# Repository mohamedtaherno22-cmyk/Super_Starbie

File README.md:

## Super Starbie ##
Super Starbie combines a Tamagotchi and an AI desktop pet into one project. Super Starbie displays monitored temperature and humidity (DHT-11), responds to button presses, and reacts to movement (MPU6050). It also features a built-in microphone (INMP411 MEMS) and a speaker, enabling TTS & STT for the AI version.

**Working Features & Features for the build week:** Theoretically, all the code is supposed to work. However, I couldn't test the firmware, especially for the AI voice chat, because I was not able to find a good emulator. I will edit the firmware and ensure that every last feature of the project works once the parts are here.

## Hardware

- **ESP32-C3 SuperMini:** MCU that processes sensor data, handles user inputs, controls the display, and provides wireless connectivity for AI features.

- **0.96" OLED Display:** A 4-pin I2C display for starbie.

- **2 Mechanical Switches:** Open the menu for the Tamagotchi, choosing options in the menu, etc.

- **MPU-6050 Motion Sensor:** A 6-axis gyroscope and accelerometer for motion detection.

- **DHT11 Temperature & Humidity Sensor:** Measures the surrounding temperature and humidity.

- **INMP441 MEMS Microphone:** An I2S digital microphone that captures audio input, enabling Speech-to-Text (STT) and voice interaction in AI mode.

- **LM386 Audio Amplifier:** Amplifies the audio signal to drive the speaker and provide audible responses.

- **Speaker:** Provides audio output for Text-to-Speech (TTS).

- **10KΩ Pull-up Resistor:**.

## BOM TABLE

| Item | Qty | Supplier | Cost/Item | Total Cost |
|---|:---:|---|---:|---:|
| MPU-6050 Gyroscope + Accelerometer | 1 | [Ram Electronics](https://www.ram-e-shop.com/shop/kit-imu-mpu6050-gy521-imu-6-dof-mpu-6050-gyroscope-accelerometer-sensor-module-7076) | $3.34 | $3.34 |
| DHT-11 Temperature & Humidity Sensor | 1 | [Ram Electronics](https://www.ram-e-shop.com/shop/sen-dht11-dht-11-temperature-humidity-sensor-asair-original-brand-7093) | $1.16 | $1.16 |
| 0.96" OLED 4-pin I2C Display | 1 | [Future Electronics](https://store.fut-electronics.com/products/1-3-128x64-oled-display-module-i-c-iic-sh1106) | $4.83 | $4.83 |
| Custom PCB | 1 | [Metanoia](https://metanoia-eg.com/pcbaf/) | $8.36 | $8.36 |
| Mechanical Keyboard Switches | 2 | [Amazon](https://www.amazon.eg/) | $1.16 | $2.32 |
| 10KΩ Resistors (2 pcs) | 1 | [Amazon](https://www.amazon.eg/) | $0.10 | $0.10 |
| ESP32-C3 SuperMini | 1 | [Amazon](https://www.amazon.eg/) | $5.95 | $5.95 |
| LM386 Audio Amplifier Module | 1 | [Ram Electronics](https://www.ram-e-shop.com/shop/kit-amp-lm386-lm386-audio-amplifier-module-200-times-gain-audio-amplifier-7424) | $0.65 | $0.65 |
| INMP441 MEMS Microphone (I2S) | 1 | [Future Electronics](https://store.fut-electronics.com/products/inmp441-mems-microphone-i2s) | $5.20 | $5.20 |
| Speaker (3W, 4Ω) | 1 | [Future Electronics](https://store.fut-electronics.com/) | $1.00 | $1.00 |
| Estimated Shipping | - | - | - | $0.00 |
| **Total** | | | | **$32.91** |

# Firmware

**Hackblub:** https://github.com/SharKingStudios/Starbie/tree/main/Firmware/Starbie

**kaloprojects:** https://github.com/techiesms/Portable-AI-Voice-Assistant-/tree/main/Portable_Voice_Assistant 

## Feautres

- **AI Assistant Mode:** Supports voice-based interactions with AI through Speech-to-Text (STT) and Text-to-Speech (TTS).

- **Tamagotchi Mode:** An interactive desktop companion.

- **Motion-Based Interactions:** Reacts to movement and changes in orientation using its motion sensor.

- **Weather & Environment Monitoring:** Displays temperature, and humidity.

## PCB & Components

## 3D Image

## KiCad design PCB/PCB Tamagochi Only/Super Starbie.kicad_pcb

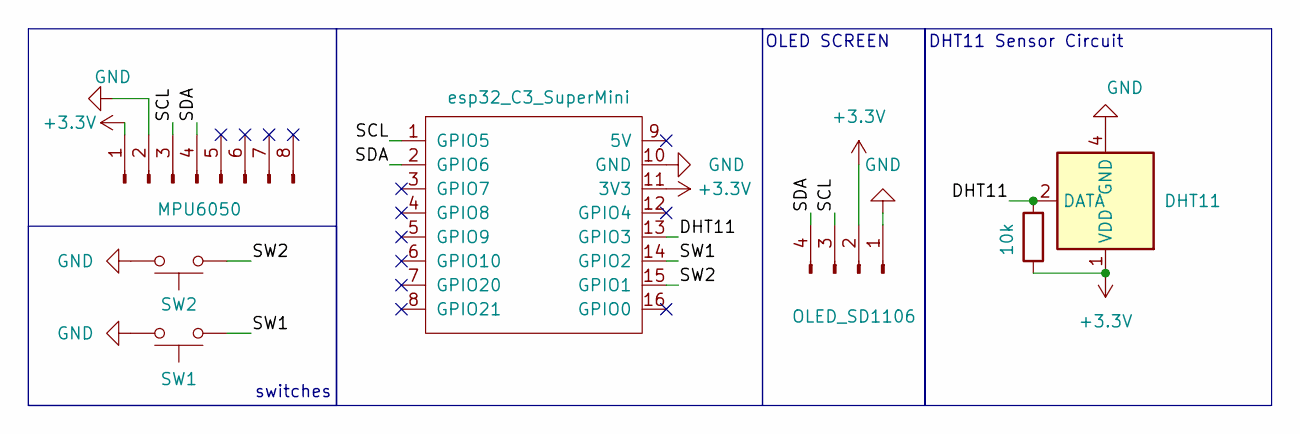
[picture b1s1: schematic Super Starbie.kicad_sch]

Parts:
J4: MPU6050; PinHeader_1x08_P2.54mm_Vertical
J5: OLED_SD1106; Display_128x64_096_I2C
MCU1: esp32_C3_SuperMini; ESP32-C3-SuperMini
R1: 10k; R_Axial_DIN0204_L3.6mm_D1.6mm_P7.62mm_Horizontal
SW1, SW2: SW_Push; SW_Cherry_MX_1.00u_PCB
U4: DHT11; Aosong_DHT11_5.5x12.0_P2.54mm

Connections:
+3.3V: J4.1, J5.2, MCU1.11 (3V3), R1.1, U4.1 (VDD)
/DHT11: MCU1.13 (GPIO3), R1.2, U4.2 (DATA)
/SCL: J4.3, J5.3, MCU1.1 (GPIO5)
/SDA: J4.4, J5.4, MCU1.2 (GPIO6)
/SW1: MCU1.14 (GPIO2), SW1.1
/SW2: MCU1.15 (GPIO1), SW2.1
GND: J4.2, J5.1, MCU1.10 (GND), SW1.2, SW2.2, U4.4 (GND)

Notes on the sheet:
switches
DHT11 Sensor Circuit
OLED SCREEN

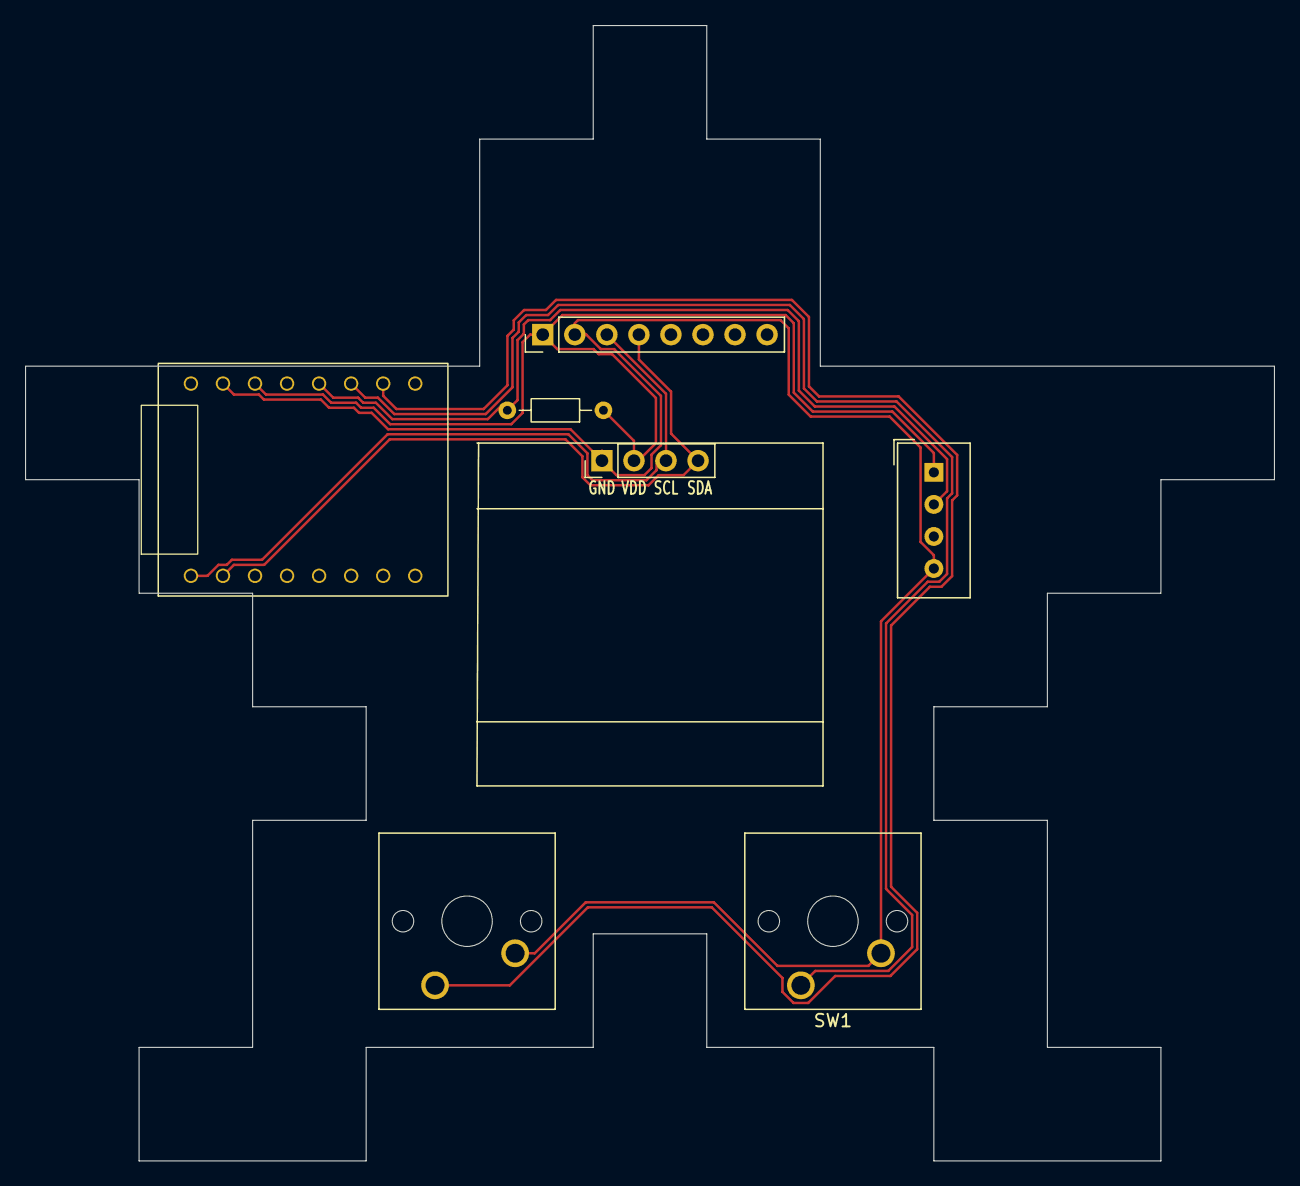
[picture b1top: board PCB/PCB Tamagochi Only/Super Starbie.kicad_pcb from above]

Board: 2 copper layers, 99.0 x 90.0 mm, 7 parts (0 on the bottom side), 7 nets.

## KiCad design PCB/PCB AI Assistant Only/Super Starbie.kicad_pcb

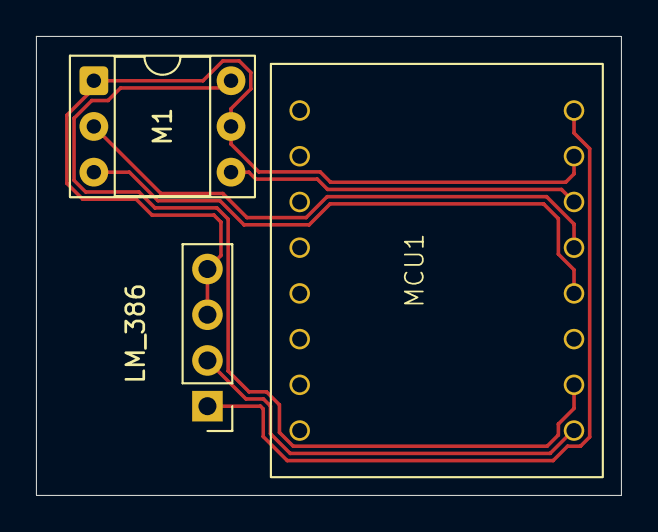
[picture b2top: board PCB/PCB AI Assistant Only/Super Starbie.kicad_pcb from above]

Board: 2 copper layers, 32.5 x 25.5 mm, 3 parts (0 on the bottom side), 7 nets.

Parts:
LM_386: PinHeader_1x04_P2.54mm_Vertical
M1: DIP-6_W7.62mm_Socket
MCU1: esp32_C3_SuperMini; ESP32-C3-SuperMini

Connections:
5V: LM_386.1 (VCC), MCU1.9 (5V)
+3.3V: M1.4 (3.3V+), MCU1.11 (3V3)
/LM386: LM_386.2 (IN), MCU1.16 (GPIO0)
/SCK: M1.3 (SCK), MCU1.13 (GPIO3)
/SD: M1.6 (SD), MCU1.15 (GPIO1)
/WS: M1.2 (WS), MCU1.12 (GPIO4)
GND: LM_386.3 (GND), LM_386.4 (GND), M1.1 (L/R), M1.5 (GND), MCU1.10 (GND)

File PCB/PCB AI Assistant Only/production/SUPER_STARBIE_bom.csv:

Designator,Footprint,Quantity,Value,LCSC Part #
LM_386,PinHeader_1x04_P2.54mm_Vertical,1,~,
M1,DIP-6_W7.62mm_Socket,1,~,
MCU1,ESP32-C3-SuperMini,1,esp32_C3_SuperMini,
